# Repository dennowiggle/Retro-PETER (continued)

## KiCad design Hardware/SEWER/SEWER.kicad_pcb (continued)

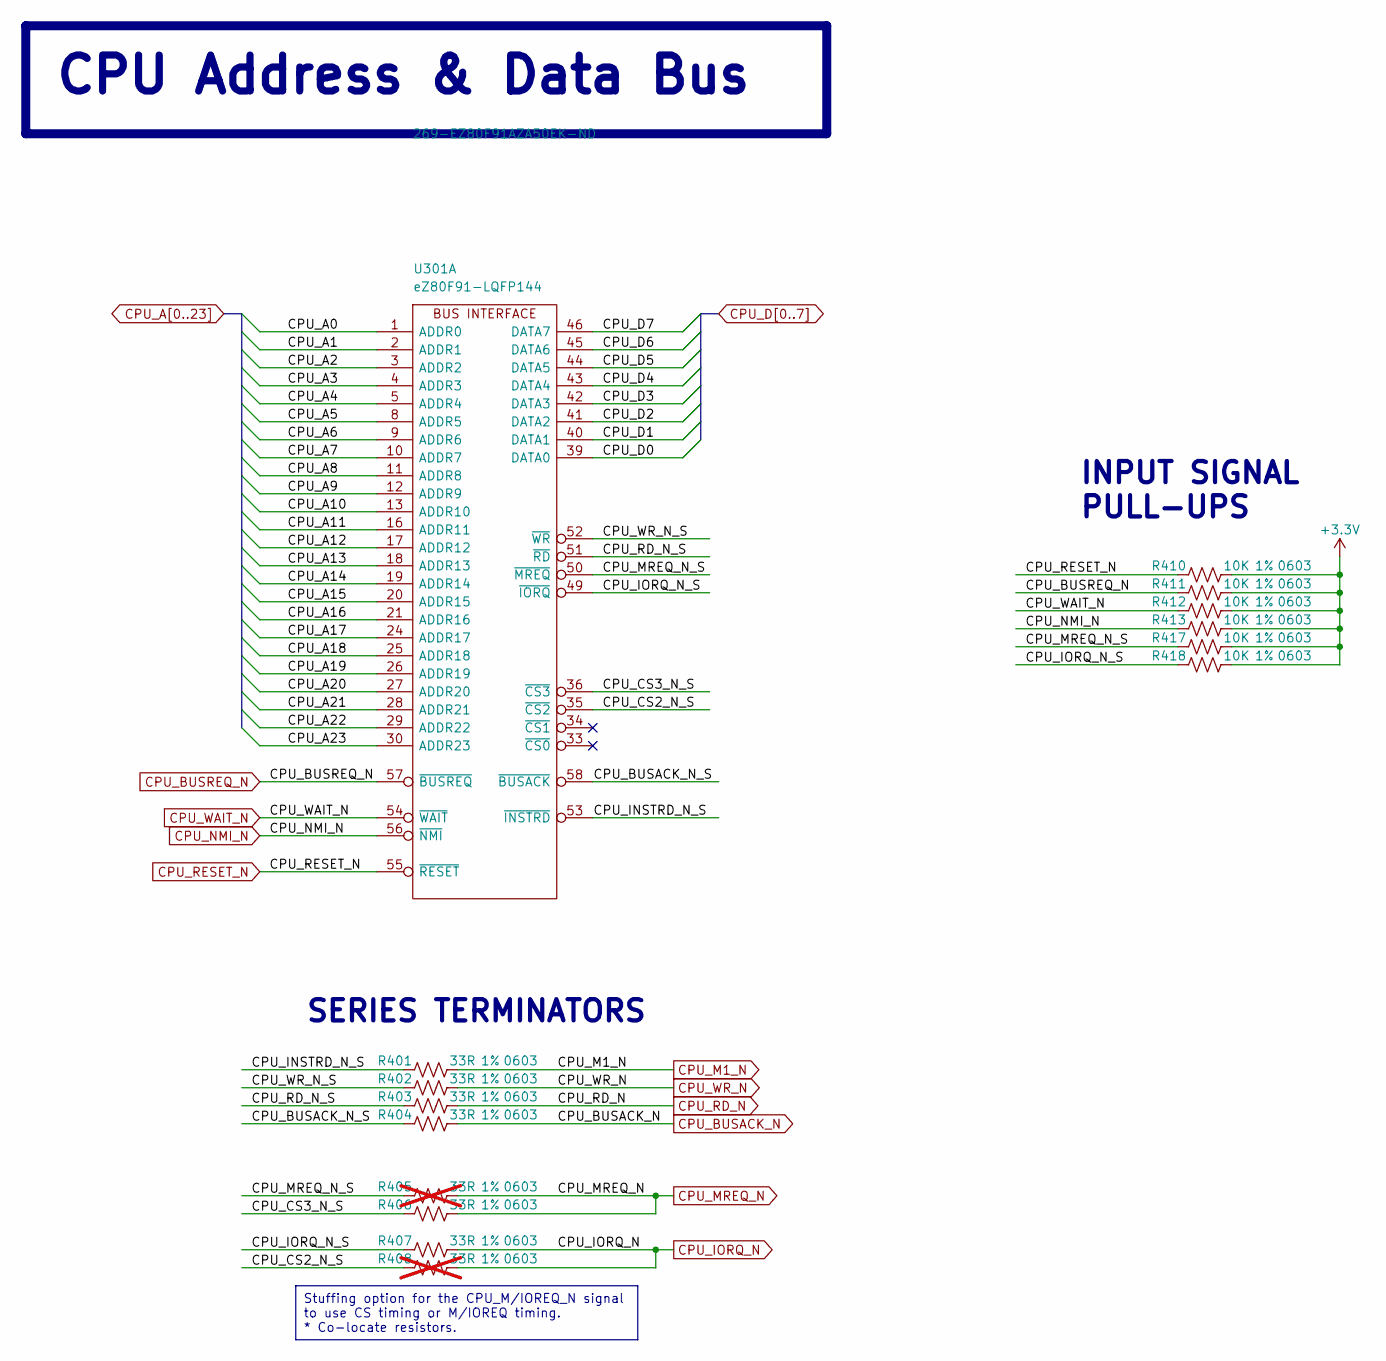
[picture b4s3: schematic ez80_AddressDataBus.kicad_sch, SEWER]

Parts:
R401, R402, R403, R404, R406, R407: 33R; R_0603_1608Metric; Tolerance 1%; MPN RC0603FR-0733RL; Digikey 13-RC0603FR-0733RLCT-ND
R405, R408: 33R; R_0603_1608Metric; Tolerance 1%; MPN RC0603FR-0733RL; Digikey 13-RC0603FR-0733RLCT-ND; not fitted
R410, R411, R412, R413, R417, R418: 10K; R_0603_1608Metric; Tolerance 1%; MPN RC0603FR-0710KL; Digikey 311-10.0KHRCT-ND
U301: eZ80F91-LQFP144; LQFP-144_20x20mm_P0.5mm; MPN EZ80F91AZA50EK; Digikey 269-EZ80F91AZA50EK-ND

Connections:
+3.3V: R410.2, R411.2, R412.2, R413.2, R417.2, R418.2; also elsewhere on the board
/CpuAddressData/CPU_BUSACK_N_S: R404.1, U301.58 (~BUSACK)
/CpuAddressData/CPU_CS2_N_S: R408.1, U301.35 (~CS2)
/CpuAddressData/CPU_CS3_N_S: R406.1, U301.36 (~CS3)
/CpuAddressData/CPU_INSTRD_N_S: R401.1, U301.53 (~INSTRD)
/CpuAddressData/CPU_IORQ_N_S: R407.1, R418.1, U301.49 (~IORQ)
/CpuAddressData/CPU_MREQ_N_S: R405.1, R417.1, U301.50 (~MREQ)
/CpuAddressData/CPU_RD_N_S: R403.1, U301.51 (~RD)
/CpuAddressData/CPU_WR_N_S: R402.1, U301.52 (~WR)
CPU_A0: U301.1 (ADDR0); also elsewhere on the board
CPU_A1: U301.2 (ADDR1); also elsewhere on the board
CPU_A2: U301.3 (ADDR2); also elsewhere on the board
CPU_A3: U301.4 (ADDR3); also elsewhere on the board
CPU_A4: U301.5 (ADDR4); also elsewhere on the board
CPU_A5: U301.8 (ADDR5); also elsewhere on the board
CPU_A6: U301.9 (ADDR6); also elsewhere on the board
CPU_A7: U301.10 (ADDR7); also elsewhere on the board
CPU_A8: U301.11 (ADDR8); also elsewhere on the board
CPU_A9: U301.12 (ADDR9); also elsewhere on the board
CPU_A10: U301.13 (ADDR10); also elsewhere on the board
CPU_A11: U301.16 (ADDR11); also elsewhere on the board
CPU_A12: U301.17 (ADDR12); also elsewhere on the board
CPU_A13: U301.18 (ADDR13); also elsewhere on the board
CPU_A14: U301.19 (ADDR14); also elsewhere on the board
CPU_A15: U301.20 (ADDR15); also elsewhere on the board
CPU_A16: U301.21 (ADDR16); also elsewhere on the board
CPU_A17: U301.24 (ADDR17); also elsewhere on the board
CPU_A18: U301.25 (ADDR18); also elsewhere on the board
CPU_A19: U301.26 (ADDR19); also elsewhere on the board
CPU_A20: U301.27 (ADDR20); also elsewhere on the board
CPU_A21: U301.28 (ADDR21); also elsewhere on the board
CPU_A22: U301.29 (ADDR22); also elsewhere on the board
CPU_A23: U301.30 (ADDR23); also elsewhere on the board
CPU_BUSACK_N: R404.2; also elsewhere on the board
CPU_BUSREQ_N: R411.1, U301.57 (~BUSREQ); also elsewhere on the board
CPU_D0: U301.39 (DATA0); also elsewhere on the board
CPU_D1: U301.40 (DATA1); also elsewhere on the board
CPU_D2: U301.41 (DATA2); also elsewhere on the board
CPU_D3: U301.42 (DATA3); also elsewhere on the board
CPU_D4: U301.43 (DATA4); also elsewhere on the board
CPU_D5: U301.44 (DATA5); also elsewhere on the board
CPU_D6: U301.45 (DATA6); also elsewhere on the board
CPU_D7: U301.46 (DATA7); also elsewhere on the board
CPU_IORQ_N: R407.2, R408.2; also elsewhere on the board
CPU_M1_N: R401.2; also elsewhere on the board
CPU_MREQ_N: R405.2, R406.2; also elsewhere on the board
CPU_NMI_N: R413.1, U301.56 (~NMI); also elsewhere on the board
CPU_RD_N: R403.2; also elsewhere on the board
CPU_RESET_N: R410.1, U301.55 (~RESET); also elsewhere on the board
CPU_WAIT_N: R412.1, U301.54 (~WAIT); also elsewhere on the board
CPU_WR_N: R402.2; also elsewhere on the board

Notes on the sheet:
CPU Address & Data Bus
Stuffing option for the CPU_M/IOREQ_N signal to use CS timing or M/IOREQ timing. * Co-locate resistors.
SERIES TERMINATORS
INPUT SIGNAL PULL-UPS

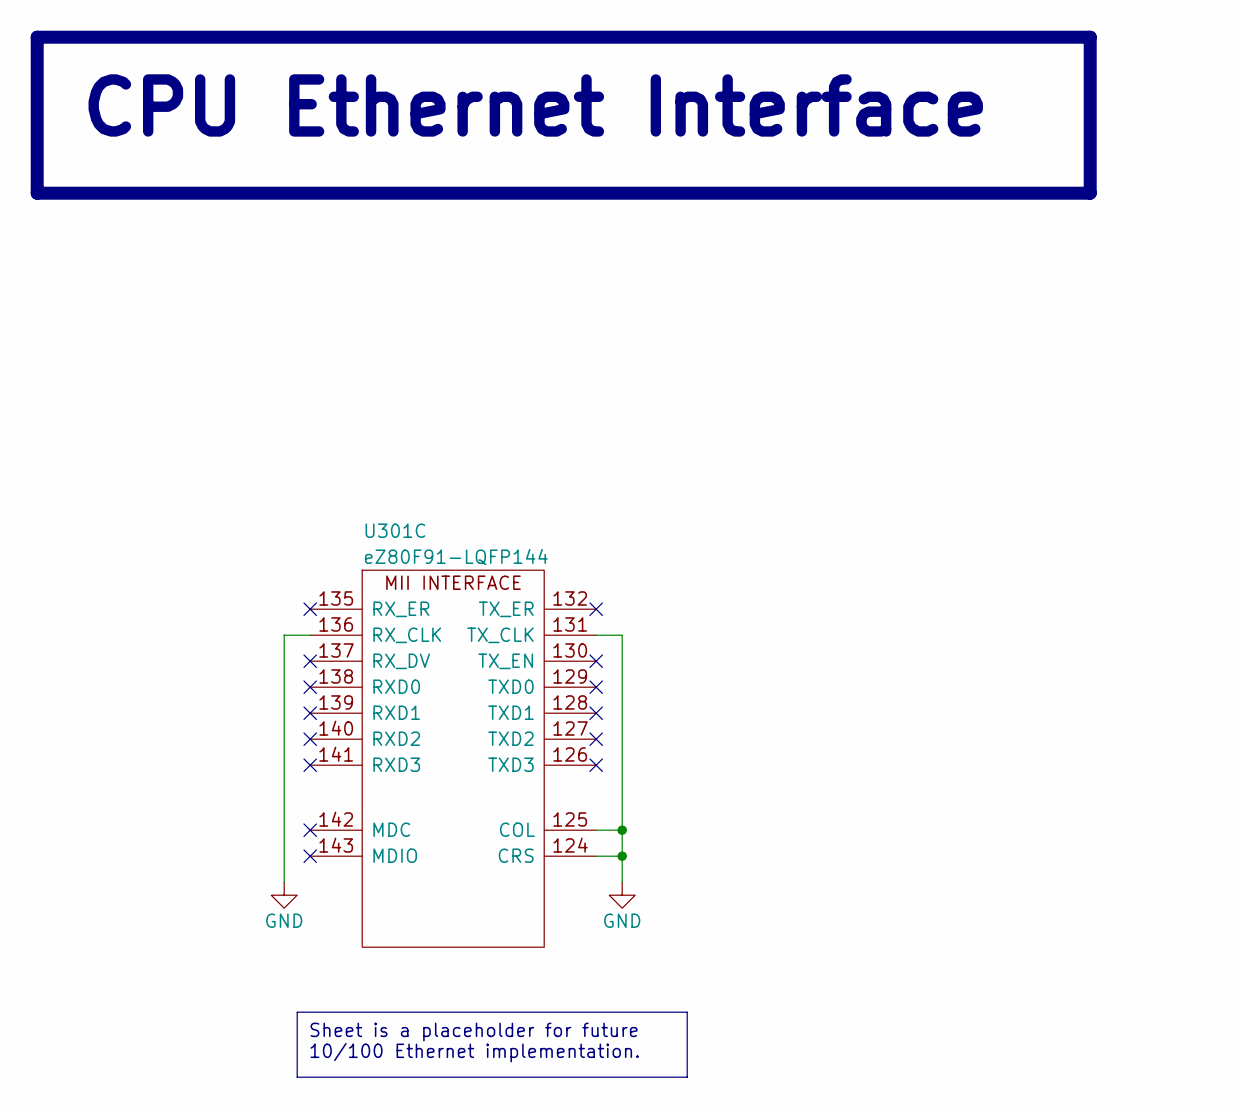
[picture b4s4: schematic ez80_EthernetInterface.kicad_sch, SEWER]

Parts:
U301: eZ80F91-LQFP144; LQFP-144_20x20mm_P0.5mm; MPN EZ80F91AZA50EK; Digikey 269-EZ80F91AZA50EK-ND

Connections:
GND: U301.124 (CRS), U301.125 (COL), U301.131 (TX_CLK), U301.136 (RX_CLK); also elsewhere on the board

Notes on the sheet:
CPU Ethernet Interface
Sheet is a placeholder for future 10/100 Ethernet implementation.

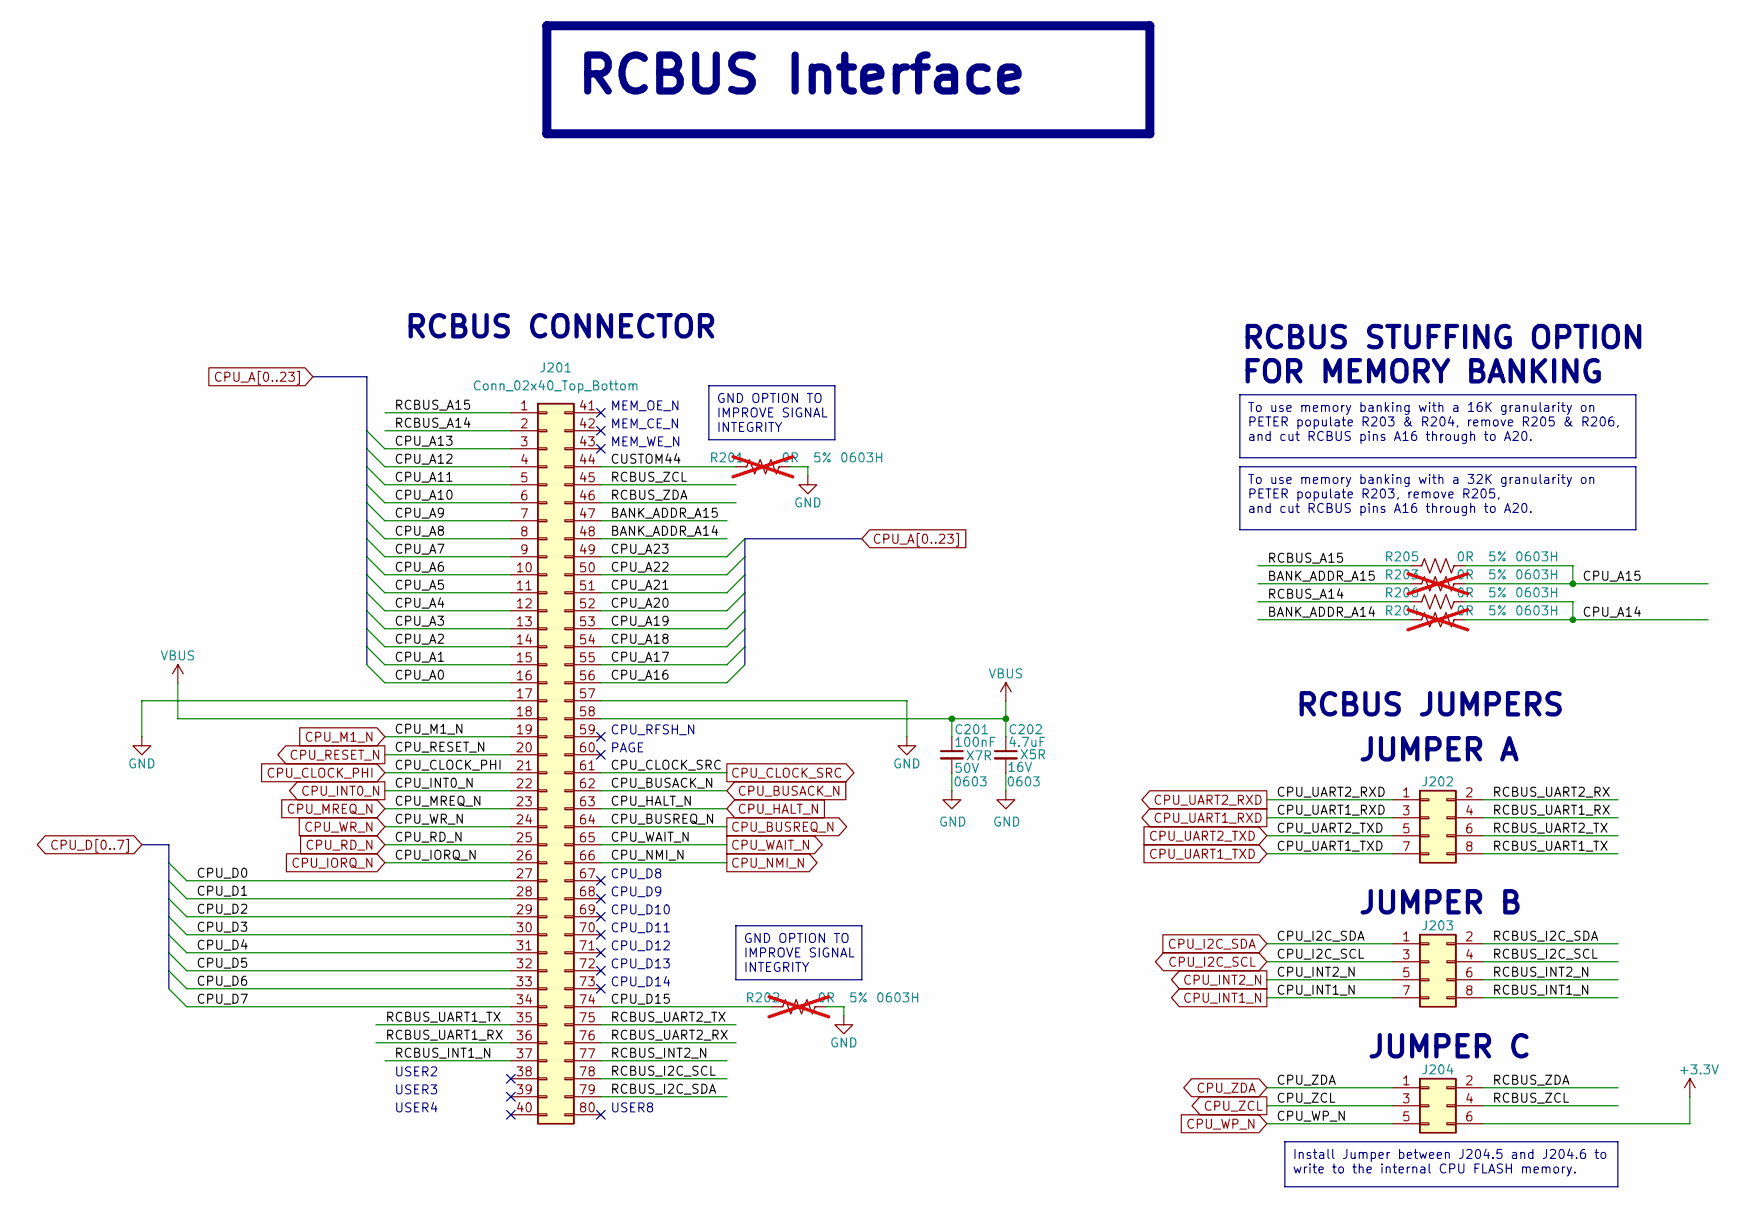
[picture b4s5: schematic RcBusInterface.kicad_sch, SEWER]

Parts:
C201: 100nF; C_0603_1608Metric; Voltage 50V; Tolerance 10%; MPN CC0603KRX7R9BB104; Digikey 311-1344-1-ND
C202: 4.7uF; C_0603_1608Metric; Voltage 16V; Tolerance 10%; MPN CL10A475KO8NNNC; Digikey 1276-1784-1-ND
J201: Conn_02x40_Top_Bottom; RCBUS_PinHeader_2x40_P2.54mm_Horizontal; MPN PH2RA-80-UA; Digikey 2057-PH2RA-80-UA-ND
J202, J203: Conn_02x04_Odd_Even; PinHeader_2x04_P2.54mm_Vertical; MPN PH2-08-UA; Digikey 2057-PH2-08-UA-ND
J204: Conn_02x03; PinHeader_2x03_P2.54mm_Vertical; MPN PH2-06-UA; Digikey 2057-PH2-06-UA-ND
R201, R202, R203, R204: 0R; R_0603_1608Metric_Pad0.98x0.95mm_HandSolder; Tolerance 5%; MPN RC0603JR-070RL; Digikey 311-0.0GRCT-ND; not fitted
R205, R206: 0R; R_0603_1608Metric_Pad0.98x0.95mm_HandSolder; Tolerance 5%; MPN RC0603JR-070RL; Digikey 311-0.0GRCT-ND

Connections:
+3.3V: J204.6; also elsewhere on the board
/RcBusInterface/BANK_ADDR_A14: J201.48, R204.1
/RcBusInterface/BANK_ADDR_A15: J201.47, R203.1
/RcBusInterface/CPU_D15: J201.74, R202.1
/RcBusInterface/CUSTOM44: J201.44, R201.1
/RcBusInterface/RCBUS_A14: J201.2, R206.1
/RcBusInterface/RCBUS_A15: J201.1, R205.1
/RcBusInterface/RCBUS_I2C_SCL: J201.78, J203.4
/RcBusInterface/RCBUS_I2C_SDA: J201.79, J203.2
/RcBusInterface/RCBUS_INT1_N: J201.37, J203.8
/RcBusInterface/RCBUS_INT2_N: J201.77, J203.6
/RcBusInterface/RCBUS_UART1_RX: J201.36, J202.4
/RcBusInterface/RCBUS_UART1_TX: J201.35, J202.8
/RcBusInterface/RCBUS_UART2_RX: J201.76, J202.2
/RcBusInterface/RCBUS_UART2_TX: J201.75, J202.6
/RcBusInterface/RCBUS_ZCL: J201.45, J204.4
/RcBusInterface/RCBUS_ZDA: J201.46, J204.2
CPU_A0: J201.16; also elsewhere on the board
CPU_A1: J201.15; also elsewhere on the board
CPU_A2: J201.14; also elsewhere on the board
CPU_A3: J201.13; also elsewhere on the board
CPU_A4: J201.12; also elsewhere on the board
CPU_A5: J201.11; also elsewhere on the board
CPU_A6: J201.10; also elsewhere on the board
CPU_A7: J201.9; also elsewhere on the board
CPU_A8: J201.8; also elsewhere on the board
CPU_A9: J201.7; also elsewhere on the board
CPU_A10: J201.6; also elsewhere on the board
CPU_A11: J201.5; also elsewhere on the board
CPU_A12: J201.4; also elsewhere on the board
CPU_A13: J201.3; also elsewhere on the board
CPU_A14: R204.2, R206.2; also elsewhere on the board
CPU_A15: R203.2, R205.2; also elsewhere on the board
CPU_A16: J201.56; also elsewhere on the board
CPU_A17: J201.55; also elsewhere on the board
CPU_A18: J201.54; also elsewhere on the board
CPU_A19: J201.53; also elsewhere on the board
CPU_A20: J201.52; also elsewhere on the board
CPU_A21: J201.51; also elsewhere on the board
CPU_A22: J201.50; also elsewhere on the board
CPU_A23: J201.49; also elsewhere on the board
CPU_BUSACK_N: J201.62; also elsewhere on the board
CPU_BUSREQ_N: J201.64; also elsewhere on the board
CPU_CLOCK_PHI: J201.21; also elsewhere on the board
CPU_CLOCK_SRC: J201.61; also elsewhere on the board
CPU_D0: J201.27; also elsewhere on the board
CPU_D1: J201.28; also elsewhere on the board
CPU_D2: J201.29; also elsewhere on the board
CPU_D3: J201.30; also elsewhere on the board
CPU_D4: J201.31; also elsewhere on the board
CPU_D5: J201.32; also elsewhere on the board
CPU_D6: J201.33; also elsewhere on the board
CPU_D7: J201.34; also elsewhere on the board
CPU_HALT_N: J201.63; also elsewhere on the board
CPU_I2C_SCL: J203.3; also elsewhere on the board
CPU_I2C_SDA: J203.1; also elsewhere on the board
CPU_INT0_N: J201.22; also elsewhere on the board
CPU_INT1_N: J203.7; also elsewhere on the board
CPU_INT2_N: J203.5; also elsewhere on the board
CPU_IORQ_N: J201.26; also elsewhere on the board
CPU_M1_N: J201.19; also elsewhere on the board
CPU_MREQ_N: J201.23; also elsewhere on the board
CPU_NMI_N: J201.66; also elsewhere on the board
CPU_RD_N: J201.25; also elsewhere on the board
CPU_RESET_N: J201.20; also elsewhere on the board
CPU_UART1_RXD: J202.3; also elsewhere on the board
CPU_UART1_TXD: J202.7; also elsewhere on the board
CPU_UART2_RXD: J202.1; also elsewhere on the board
CPU_UART2_TXD: J202.5; also elsewhere on the board
CPU_WAIT_N: J201.65; also elsewhere on the board
CPU_WP_N: J204.5; also elsewhere on the board
CPU_WR_N: J201.24; also elsewhere on the board
CPU_ZCL: J204.3; also elsewhere on the board
CPU_ZDA: J204.1; also elsewhere on the board
GND: C201.2, C202.2, J201.17, J201.57, R201.2, R202.2; also elsewhere on the board
VBUS: C201.1, C202.1, J201.18, J201.58; also elsewhere on the board

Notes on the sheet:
GND OPTION TO IMPROVE SIGNAL INTEGRITY
Install Jumper between J204.5 and J204.6 to write to the internal CPU FLASH memory.
To use memory banking with a 32K granularity on PETER populate R203, remove R205, and cut RCBUS pins A16 through to A20.
RCBUS Interface
To use memory banking with a 16K granularity on PETER populate R203 & R204, remove R205 & R206, and cut RCBUS pins A16 through to A20.
MEM_OE_N
MEM_WE_N
CPU_RFSH_N
CPU_D11
RCBUS CONNECTOR
CPU_D8
CPU_D14
CPU_D12
JUMPER B
USER2
USER4
JUMPER C
USER3
JUMPER A
MEM_CE_N
CPU_D9
USER8
CPU_D13
PAGE
RCBUS JUMPERS
RCBUS STUFFING OPTION FOR MEMORY BANKING
CPU_D10

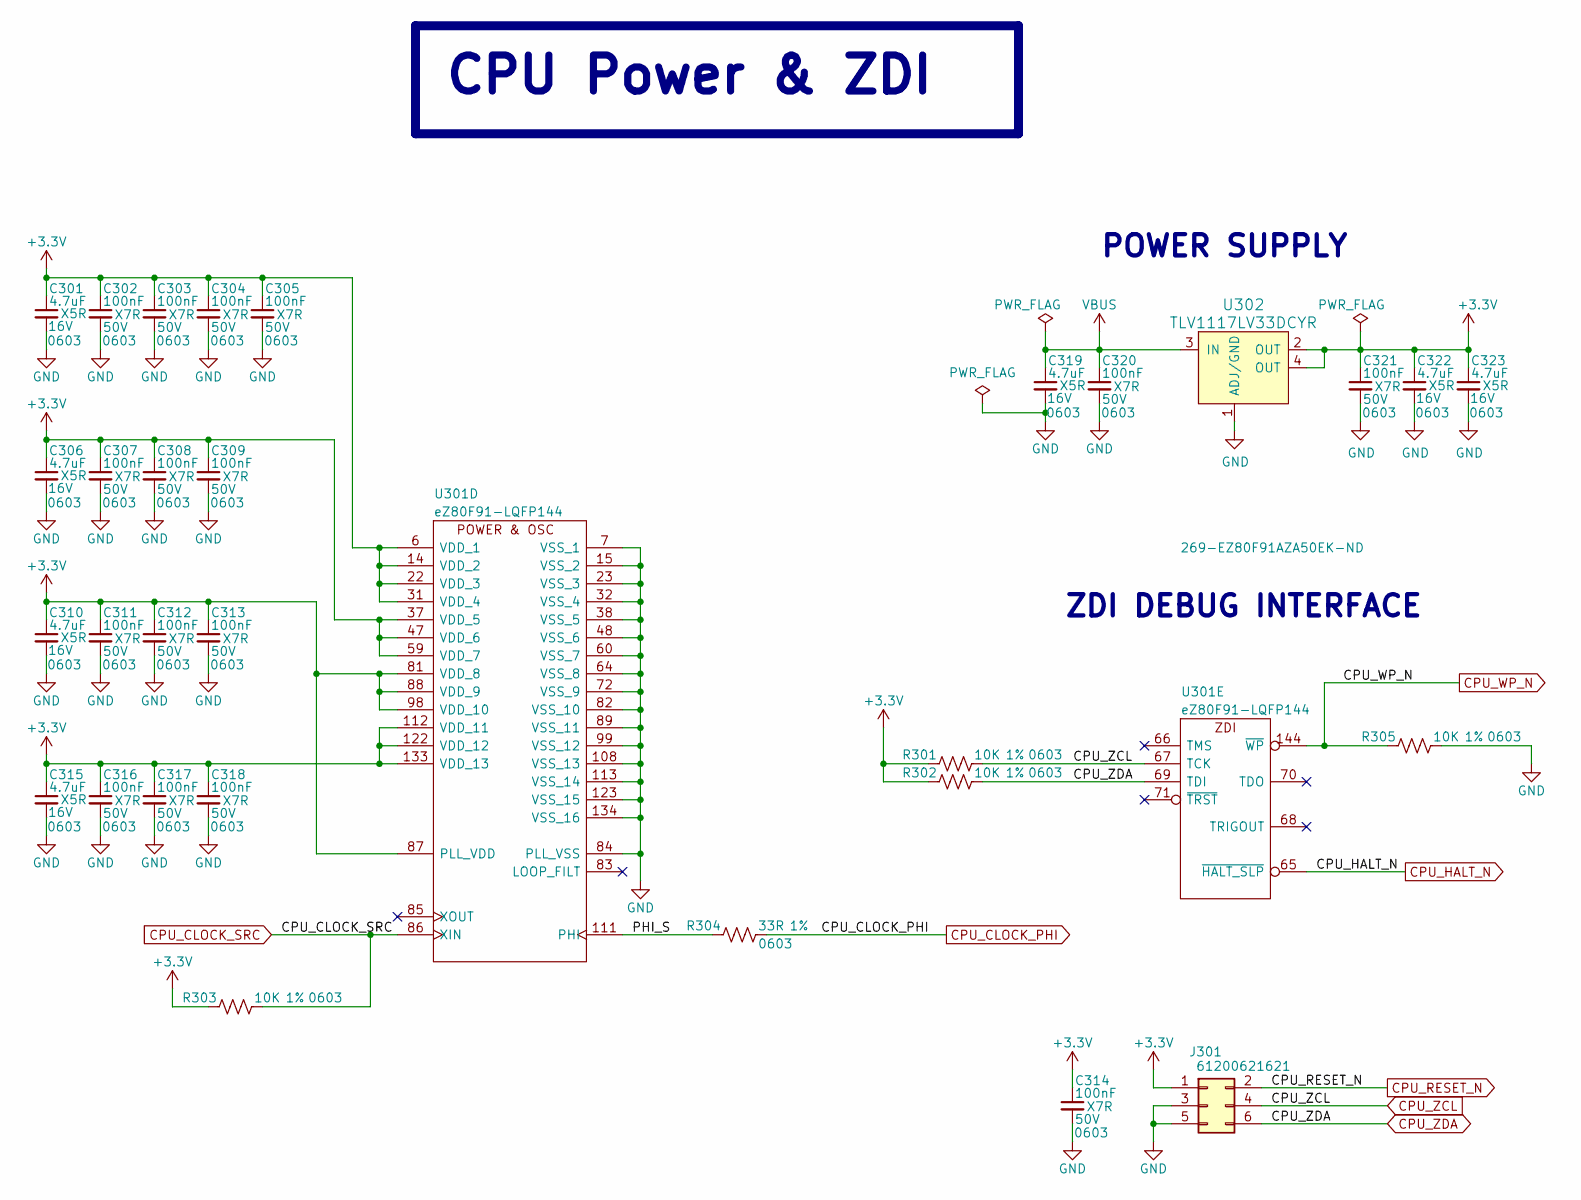
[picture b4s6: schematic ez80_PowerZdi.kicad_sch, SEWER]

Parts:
C301, C306, C310, C315, C319, C322, C323: 4.7uF; C_0603_1608Metric; Voltage 16V; Tolerance 10%; MPN CL10A475KO8NNNC; Digikey 1276-1784-1-ND
C302, C303, C304, C305, C307, C308, C309, C311, C312, C313, C314, C316, C317, C318, C320, C321: 100nF; C_0603_1608Metric; Voltage 50V; Tolerance 10%; MPN CC0603KRX7R9BB104; Digikey 311-1344-1-ND
J301: 61200621621; Wurth_61200621621; MPN 61200621621; Digikey 732-5394-ND
R301, R302, R303, R305: 10K; R_0603_1608Metric; Tolerance 1%; MPN RC0603FR-0710KL; Digikey 311-10.0KHRCT-ND
R304: 33R; R_0603_1608Metric; Tolerance 1%; MPN RC0603FR-0733RL; Digikey 13-RC0603FR-0733RLCT-ND
U301: eZ80F91-LQFP144; LQFP-144_20x20mm_P0.5mm; MPN EZ80F91AZA50EK; Digikey 269-EZ80F91AZA50EK-ND
U302: TLV1117LV33DCYR; SOT-223; MPN TLV1117LV33DCYR; Digikey 296-28778-1-ND

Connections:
+3.3V: C301.1, C302.1, C303.1, C304.1, C305.1, C306.1, C307.1, C308.1, C309.1, C310.1, C311.1, C312.1, C313.1, C314.1, C315.1, C316.1, C317.1, C318.1, C321.1, C322.1, C323.1, J301.1, R301.1, R302.1, R303.1, U301.6 (VDD_1), U301.14 (VDD_2), U301.22 (VDD_3), U301.31 (VDD_4), U301.37 (VDD_5), U301.47 (VDD_6), U301.59 (VDD_7), U301.81 (VDD_8), U301.87 (PLL_VDD), U301.88 (VDD_9), U301.98 (VDD_10), U301.112 (VDD_11), U301.122 (VDD_12), U301.133 (VDD_13), U302.2 (OUT), U302.4 (OUT); also elsewhere on the board
/CpuPowerZdi/PHI_S: R304.1, U301.111 (PHI)
CPU_CLOCK_PHI: R304.2; also elsewhere on the board
CPU_CLOCK_SRC: R303.2, U301.86 (XIN); also elsewhere on the board
CPU_HALT_N: U301.65 (~HALT_SLP); also elsewhere on the board
CPU_RESET_N: J301.2; also elsewhere on the board
CPU_WP_N: R305.1, U301.144 (~WP); also elsewhere on the board
CPU_ZCL: J301.4, R301.2, U301.67 (TCK); also elsewhere on the board
CPU_ZDA: J301.6, R302.2, U301.69 (TDI); also elsewhere on the board
GND: C301.2, C302.2, C303.2, C304.2, C305.2, C306.2, C307.2, C308.2, C309.2, C310.2, C311.2, C312.2, C313.2, C314.2, C315.2, C316.2, C317.2, C318.2, C319.2, C320.2, C321.2, C322.2, C323.2, J301.3, J301.5, R305.2, U301.7 (VSS_1), U301.15 (VSS_2), U301.23 (VSS_3), U301.32 (VSS_4), U301.38 (VSS_5), U301.48 (VSS_6), U301.60 (VSS_7), U301.64 (VSS_8), U301.72 (VSS_9), U301.82 (VSS_10), U301.84 (PLL_VSS), U301.89 (VSS_11), U301.99 (VSS_12), U301.108 (VSS_13), U301.113 (VSS_14), U301.123 (VSS_15), U301.134 (VSS_16), U302.1 (ADJ/GND); also elsewhere on the board
VBUS: C319.1, C320.1, U302.3 (IN); also elsewhere on the board

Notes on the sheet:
CPU Power & ZDI
ZDI DEBUG INTERFACE
POWER SUPPLY

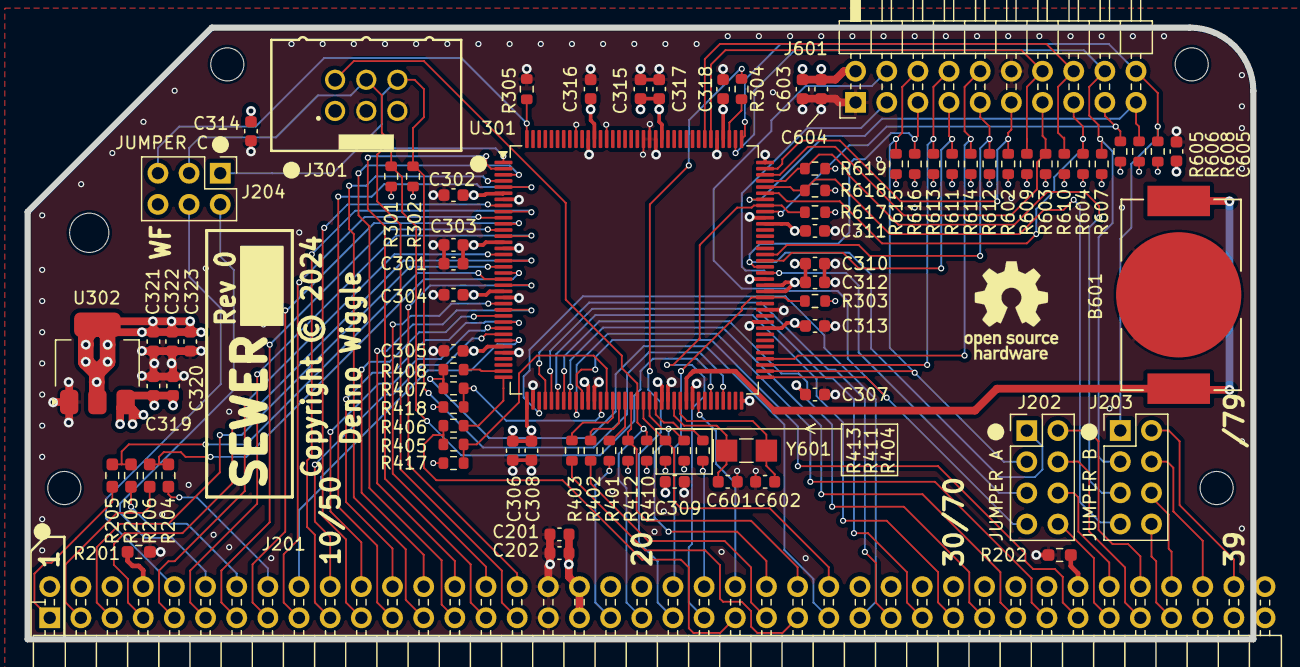
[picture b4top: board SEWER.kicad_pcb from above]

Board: 4 copper layers, 99.9 x 49.9 mm, 90 parts (1 on the bottom side), 99 nets.

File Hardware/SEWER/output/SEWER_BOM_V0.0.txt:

Reference,Value,Footprint,Qty,DNP,Digikey,Footprint2,LCSC Part #,MPN,Description
U302,TLV1117LV33DCYR,Package_TO_SOT_SMD:SOT-223,1,,296-28778-1-ND,,C15578,TLV1117LV33DCYR,IC REG LINEAR 3.3V 1A SOT223-4
"R205,R206",0R,Resistor_SMD:R_0603_1608Metric_Pad0.98x0.95mm_HandSolder,2,,311-0.0GRCT-ND,0603H,C95177,RC0603JR-070RL,RES 0 OHM 5% 1/10W 0603
"R201,R202,R203,R204",0R,Resistor_SMD:R_0603_1608Metric_Pad0.98x0.95mm_HandSolder,4,DNP,311-0.0GRCT-ND,0603H,C95177,RC0603JR-070RL,RES 0 OHM 5% 1/10W 0603
"R405,R408",33R,Resistor_SMD:R_0603_1608Metric,2,DNP,13-RC0603FR-0733RLCT-ND,603,C108661,RC0603FR-0733RL,RES 33 OHM 1% 1/10W 0603
"R304,R401,R402,R403,R404,R406,R407",33R,Resistor_SMD:R_0603_1608Metric,7,,13-RC0603FR-0733RLCT-ND,603,C108661,RC0603FR-0733RL,RES 33 OHM 1% 1/10W 0603
"R301,R302,R303,R305,R410,R411,R412,R413,R417,R418,R602,R603,R604,R605,R606,R607,R608,R609,R610,R611,R612,R613,R614,R615,R616,R617,R618,R619",10K,Resistor_SMD:R_0603_1608Metric,28,,311-10.0KHRCT-ND,603,C98220,RC0603FR-0710KL,RES 10K OHM 1% 1/10W 0603
J201,Conn_02x40_Top_Bottom,WTM_Library:RCBUS_PinHeader_2x40_P2.54mm_Horizontal,1,,2057-PH2RA-80-UA-ND,,,PH2RA-80-UA,CONN HEADER R/A 80POS 2.54MM
J601,Conn_02x10_Odd_Even,Connector_PinHeader_2.54mm:PinHeader_2x10_P2.54mm_Horizontal,1,,2057-PH2RA-20-UA-ND,,,PH2RA-20-UA,CONN HEADER HORIZONTAL 20POS 2.54MM
"J202,J203",Conn_02x04_Odd_Even,Connector_PinHeader_2.54mm:PinHeader_2x04_P2.54mm_Vertical,2,,2057-PH2-08-UA-ND,,,PH2-08-UA,CONN HEADER VERT 8POS 2.54MM
J204,Conn_02x03,Connector_PinHeader_2.54mm:PinHeader_2x03_P2.54mm_Vertical,1,,2057-PH2-06-UA-ND,,,PH2-06-UA,CONN HEADER VERT 6POS 2.54MM
U301,eZ80F91-LQFP144,Package_QFP:LQFP-144_20x20mm_P0.5mm,1,,269-EZ80F91AZA50EK-ND,,C3215893,EZ80F91AZA50EK,"Zilog 8/16-bit Microcontrollers - MCU 50/20MHz I/O -32, 2 UARTs w/ IrDA, I²C, SPI RAM 8k 256K flash"
Y601,ECX-.327-CDX-1293,Crystal:Crystal_SMD_EuroQuartz_EQ161-2Pin_3.2x1.5mm_HandSoldering,1,,XC2292CT-ND,,C2450907,ECX-.327-CDX-1293,CRYSTAL 32.7680KHZ 5PPM 12.5PF SMD
"C601,C602",12pF,Capacitor_SMD:C_0603_1608Metric,2,,1276-1254-1-ND,603,C38523,CL10C120JB8NNNC,CAP CER 12PF 5% 50V C0G/NP0 0603
"C202,C301,C306,C310,C315,C319,C322,C323,C603",4.7uF,Capacitor_SMD:C_0603_1608Metric,9,,1276-1784-1-ND,603,C19666,CL10A475KO8NNNC,CAP CER 4.7UF 16V X5R 0603
"C201,C302,C303,C304,C305,C307,C308,C309,C311,C312,C313,C314,C316,C317,C318,C320,C321,C604,C605",100nF,Capacitor_SMD:C_0603_1608Metric,19,,311-1344-1-ND,603,C14663,CC0603KRX7R9BB104,CAP CER 0.1UF 50V X7R 0603
B601,BAT-HLD-012-SMT,WTM_Library:BAT-HLD-012-SMT_TEC,1,,BAT-HLD-012-SMT-ND,,C22418383,BAT-HLD-012-SMT,BATT RETAINER COIN 12MM 1CEL SMD
J301,61200621621,WTM_Library:Wurth_61200621621,1,,732-5394-ND,,,61200621621,CONN HEADER SHROUDED VERT 6POS 2.54MM

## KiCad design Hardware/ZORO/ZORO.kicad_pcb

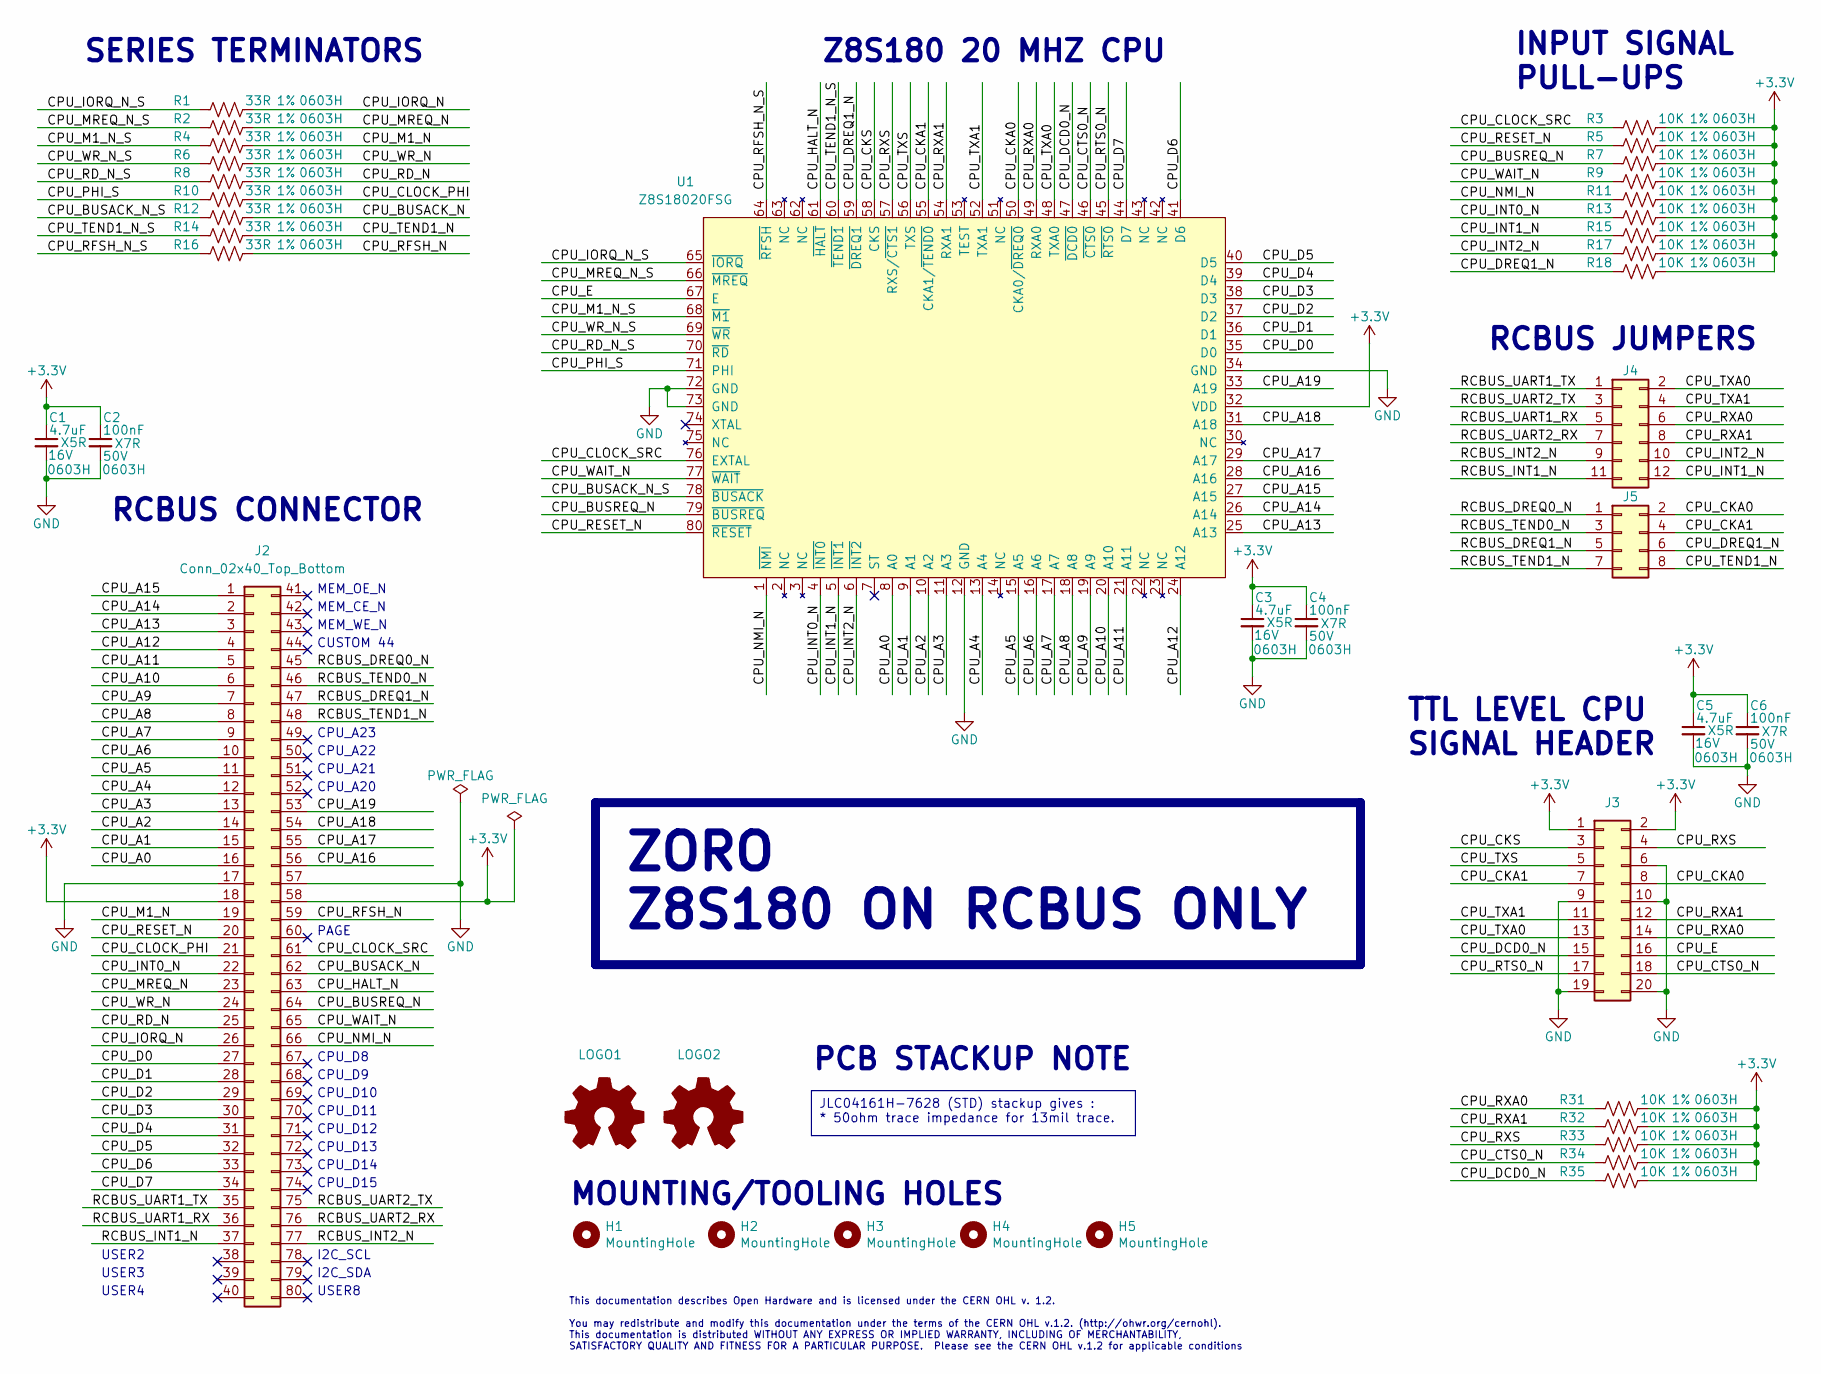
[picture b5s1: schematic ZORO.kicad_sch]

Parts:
C1, C3, C5: 4.7uF; C_0603_1608Metric_Pad1.08x0.95mm_HandSolder; Voltage 16V; Tolerance 10%; MPN CL10A475KO8NNNC; Digikey 1276-1784-1-ND
C2, C4, C6: 100nF; C_0603_1608Metric_Pad1.08x0.95mm_HandSolder; Voltage 50V; Tolerance 10%; MPN CC0603KRX7R9BB104; Digikey 311-1344-1-ND
H1: MountingHole; MountingHole_3.2mm_M3
H2, H3, H4, H5: MountingHole; MountingHole_2.7mm_M2.5_DIN965
J2: Conn_02x40_Top_Bottom; RCBUS_PinHeader_2x40_P2.54mm_Horizontal; MPN 9-103795-0; Digikey A34274-40-ND
J3: Conn_02x10_Odd_Even; PinHeader_2x10_P2.54mm_Horizontal; MPN PH2RA-20-UA; Digikey 2057-PH2RA-20-UA-ND
J4: Conn_02x06_Odd_Even; PinHeader_2x06_P2.54mm_Vertical; MPN PH2-12-UA; Digikey 2057-PH2-12-UA-ND
J5: Conn_02x04_Odd_Even; PinHeader_2x04_P2.54mm_Vertical; MPN PH2-08-UA; Digikey 2057-PH2-08-UA-ND
LOGO1, LOGO2: Logo_Open_Hardware_Small; OSHW-Logo_7.5x8mm_SilkScreen
R1, R2, R4, R6, R8, R10, R12, R14, R16: 33R; R_0603_1608Metric_Pad0.98x0.95mm_HandSolder; Tolerance 1%; MPN RC0603FR-0733RL; Digikey 13-RC0603FR-0733RLCT-ND
R3, R5, R7, R9, R11, R13, R15, R17, R18, R31, R32, R33, R34, R35: 10K; R_0603_1608Metric_Pad0.98x0.95mm_HandSolder; Tolerance 1%; MPN RC0603FR-0710KL; Digikey 311-10.0KHRCT-ND
U1: Z8S18020FSG; PQFP-80_14x20mm_P0.8mm; MPN Z8S18020FSG; Digikey 269-4541-5-ND

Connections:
+3.3V: C1.1, C2.1, C3.1, C4.1, C5.1, C6.1, J2.18, J2.58, J3.1, J3.2, R3.2, R5.2, R7.2, R9.2, R11.2, R13.2, R15.2, R17.2, R18.2, R31.2, R32.2, R33.2, R34.2, R35.2, U1.32 (VDD)
/CPU_A0: J2.16, U1.8 (A0)
/CPU_A1: J2.15, U1.9 (A1)
/CPU_A2: J2.14, U1.10 (A2)
/CPU_A3: J2.13, U1.11 (A3)
/CPU_A4: J2.12, U1.13 (A4)
/CPU_A5: J2.11, U1.15 (A5)
/CPU_A6: J2.10, U1.16 (A6)
/CPU_A7: J2.9, U1.17 (A7)
/CPU_A8: J2.8, U1.18 (A8)
/CPU_A9: J2.7, U1.19 (A9)
/CPU_A10: J2.6, U1.20 (A10)
/CPU_A11: J2.5, U1.21 (A11)
/CPU_A12: J2.4, U1.24 (A12)
/CPU_A13: J2.3, U1.25 (A13)
/CPU_A14: J2.2, U1.26 (A14)
/CPU_A15: J2.1, U1.27 (A15)
/CPU_A16: J2.56, U1.28 (A16)
/CPU_A17: J2.55, U1.29 (A17)
/CPU_A18: J2.54, U1.31 (A18)
/CPU_A19: J2.53, U1.33 (A19)
/CPU_BUSACK_N: J2.62, R12.2
/CPU_BUSACK_N_S: R12.1, U1.78 (~BUSACK)
/CPU_BUSREQ_N: J2.64, R7.1, U1.79 (~BUSREQ)
/CPU_CKA0: J3.8, J5.2, U1.50 (CKA0/~DREQ0)
/CPU_CKA1: J3.7, J5.4, U1.55 (CKA1/~TEND0)
/CPU_CKS: J3.3, U1.58 (CKS)
/CPU_CLOCK_PHI: J2.21, R10.2
/CPU_CLOCK_SRC: J2.61, R3.1, U1.76 (EXTAL)
/CPU_CTS0_N: J3.18, R34.1, U1.46 (~CTS0)
/CPU_D0: J2.27, U1.35 (D0)
/CPU_D1: J2.28, U1.36 (D1)
/CPU_D2: J2.29, U1.37 (D2)
/CPU_D3: J2.30, U1.38 (D3)
/CPU_D4: J2.31, U1.39 (D4)
/CPU_D5: J2.32, U1.40 (D5)
/CPU_D6: J2.33, U1.41 (D6)
/CPU_D7: J2.34, U1.44 (D7)
/CPU_DCD0_N: J3.15, R35.1, U1.47 (~DCD0)
/CPU_DREQ1_N: J5.6, R18.1, U1.59 (~DREQ1)
/CPU_E: J3.16, U1.67 (E)
/CPU_HALT_N: J2.63, U1.61 (~HALT)
/CPU_INT0_N: J2.22, R13.1, U1.4 (~INT0)
/CPU_INT1_N: J4.12, R15.1, U1.5 (~INT1)
/CPU_INT2_N: J4.10, R17.1, U1.6 (~INT2)
/CPU_IORQ_N: J2.26, R1.2
/CPU_IORQ_N_S: R1.1, U1.65 (~IORQ)
/CPU_M1_N: J2.19, R4.2
/CPU_M1_N_S: R4.1, U1.68 (~M1)
/CPU_MREQ_N: J2.23, R2.2
/CPU_MREQ_N_S: R2.1, U1.66 (~MREQ)
/CPU_NMI_N: J2.66, R11.1, U1.1 (~NMI)
/CPU_PHI_S: R10.1, U1.71 (PHI)
/CPU_RD_N: J2.25, R8.2
/CPU_RD_N_S: R8.1, U1.70 (~RD)
/CPU_RESET_N: J2.20, R5.1, U1.80 (~RESET)
/CPU_RFSH_N: J2.59, R16.2
/CPU_RFSH_N_S: R16.1, U1.64 (~RFSH)
/CPU_RTS0_N: J3.17, U1.45 (~RTS0)
/CPU_RXA0: J3.14, J4.6, R31.1, U1.49 (RXA0)
/CPU_RXA1: J3.12, J4.8, R32.1, U1.54 (RXA1)
/CPU_RXS: J3.4, R33.1, U1.57 (RXS/~CTS1)
/CPU_TEND1_N: J5.8, R14.2
/CPU_TEND1_N_S: R14.1, U1.60 (~TEND1)
/CPU_TXA0: J3.13, J4.2, U1.48 (TXA0)
/CPU_TXA1: J3.11, J4.4, U1.52 (TXA1)
/CPU_TXS: J3.5, U1.56 (TXS)
/CPU_WAIT_N: J2.65, R9.1, U1.77 (~WAIT)
/CPU_WR_N: J2.24, R6.2
/CPU_WR_N_S: R6.1, U1.69 (~WR)
/RCBUS_DREQ0_N: J2.45, J5.1
/RCBUS_DREQ1_N: J2.47, J5.5
/RCBUS_INT1_N: J2.37, J4.11
/RCBUS_INT2_N: J2.77, J4.9
/RCBUS_TEND0_N: J2.46, J5.3
/RCBUS_TEND1_N: J2.48, J5.7
/RCBUS_UART1_RX: J2.36, J4.5
/RCBUS_UART1_TX: J2.35, J4.1
/RCBUS_UART2_RX: J2.76, J4.7
/RCBUS_UART2_TX: J2.75, J4.3
GND: C1.2, C2.2, C3.2, C4.2, C5.2, C6.2, J2.17, J2.57, J3.6, J3.9, J3.10, J3.19, J3.20, U1.12 (GND), U1.34 (GND), U1.72 (GND), U1.73 (GND)

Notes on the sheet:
ZORO Z8S180 ON RCBUS ONLY
JLC04161H-7628 (STD) stackup gives : * 50ohm trace impedance for 13mil trace.
I2C_SDA
MEM_CE_N
USER3
SERIES TERMINATORS
CPU_D14
MEM_OE_N
Z8S180 20 MHZ CPU
RCBUS CONNECTOR
CPU_D13
CUSTOM 44
CPU_D12
CPU_A23
TTL LEVEL CPU SIGNAL HEADER
INPUT SIGNAL PULL-UPS
CPU_D11
CPU_D9
USER8
CPU_A22
MOUNTING/TOOLING HOLES
This documentation describes Open Hardware and is licensed under the CERN OHL v. 1.2. You may redistribute and modify this documentation under the terms of the CERN OHL v.1.2. (http://ohwr.org/cernohl). This documentation is distributed WITHOUT ANY EXPRESS OR IMPLIED WARRANTY, INCLUDING OF MERCHANT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
I2C_SCL
USER4
USER2
MEM_WE_N
RCBUS JUMPERS
CPU_D8
CPU_A21
CPU_A20
CPU_D15
PAGE
PCB STACKUP NOTE
CPU_D10
